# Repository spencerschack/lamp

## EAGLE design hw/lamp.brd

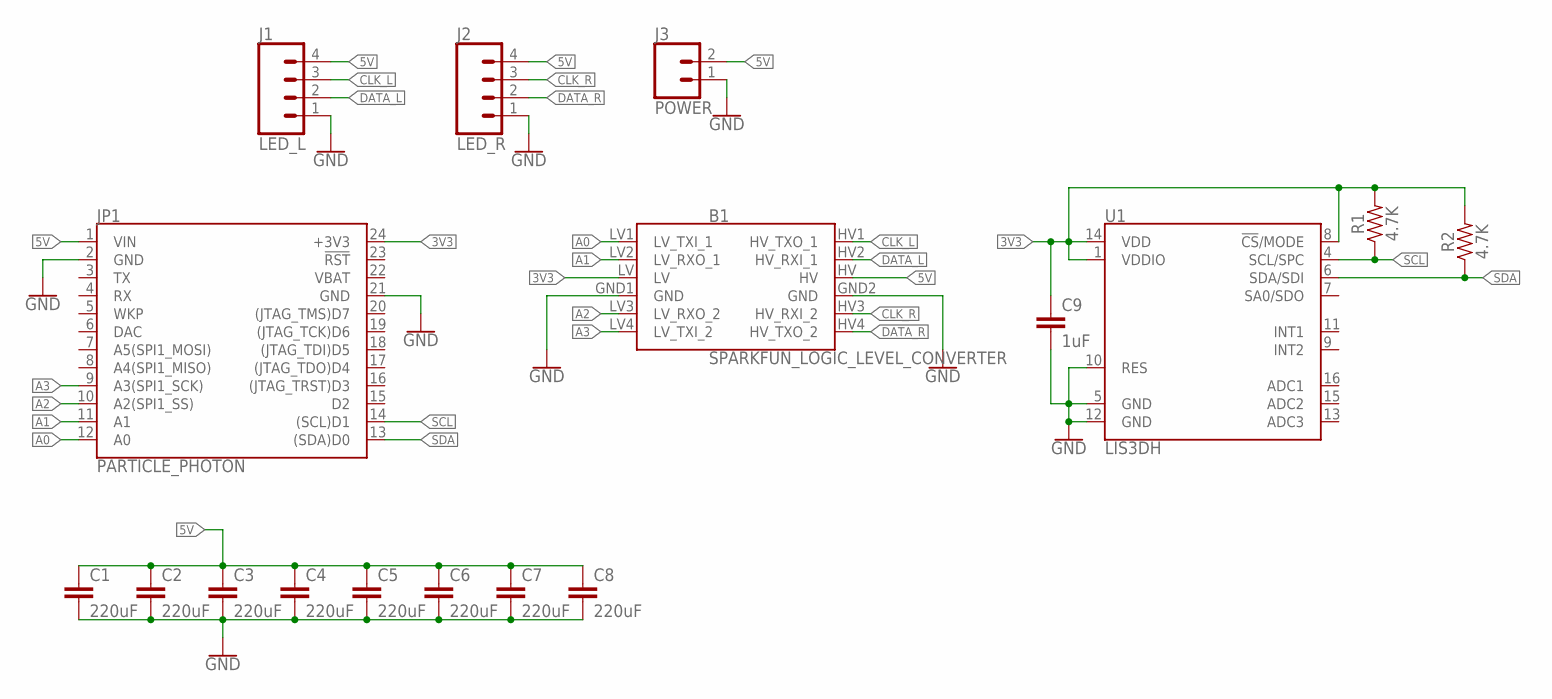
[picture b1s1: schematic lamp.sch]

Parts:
B1: SPARKFUN_LOGIC_LEVEL_CONVERTER
C1, C2, C3, C4, C5, C6, C7, C8: 220uF; 1206
C9: 1uF; 0603
J1: LED_L; 1X04_LONGPADS
J2: LED_R; 1X04_LONGPADS
J3: POWER; 1X02_LOCK_LONGPADS
JP1: PARTICLE_PHOTON
R1, R2: 4.7K; 0603
U1: LIS3DH; LGA-16-3X3

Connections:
3V3: B1.LV, C9.1, JP1.24 (+3V3), R1.2, R2.2, U1.1 (VDDIO), U1.8 (!CS!/MODE), U1.14 (VDD)
5V: B1.HV, C1.1, C2.1, C3.1, C4.1, C5.1, C6.1, C7.1, C8.1, J1.4, J2.4, J3.2, JP1.1 (VIN)
A0: B1.LV1 (LV_TXI_1), JP1.12 (A0)
A1: B1.LV2 (LV_RXO_1), JP1.11 (A1)
A2: B1.LV3 (LV_RXO_2), JP1.10 (A2(SPI1_SS))
A3: B1.LV4 (LV_TXI_2), JP1.9 (A3(SPI1_SCK))
CLK_L: B1.HV1 (HV_TXO_1), J1.3
CLK_R: B1.HV3 (HV_RXI_2), J2.3
DATA_L: B1.HV2 (HV_RXI_1), J1.2
DATA_R: B1.HV4 (HV_TXO_2), J2.2
GND: B1.GND1 (GND), B1.GND2 (GND), C1.2, C2.2, C3.2, C4.2, C5.2, C6.2, C7.2, C8.2, C9.2, J1.1, J2.1, J3.1, JP1.2 (GND), JP1.21 (GND), U1.5 (GND), U1.10 (RES), U1.12 (GND)
SCL: JP1.14 ((SCL)D1), R1.1, U1.4 (SCL/SPC)
SDA: JP1.13 ((SDA)D0), R2.1, U1.6 (SDA/SDI)
VBAT: JP1.22 (VBAT)

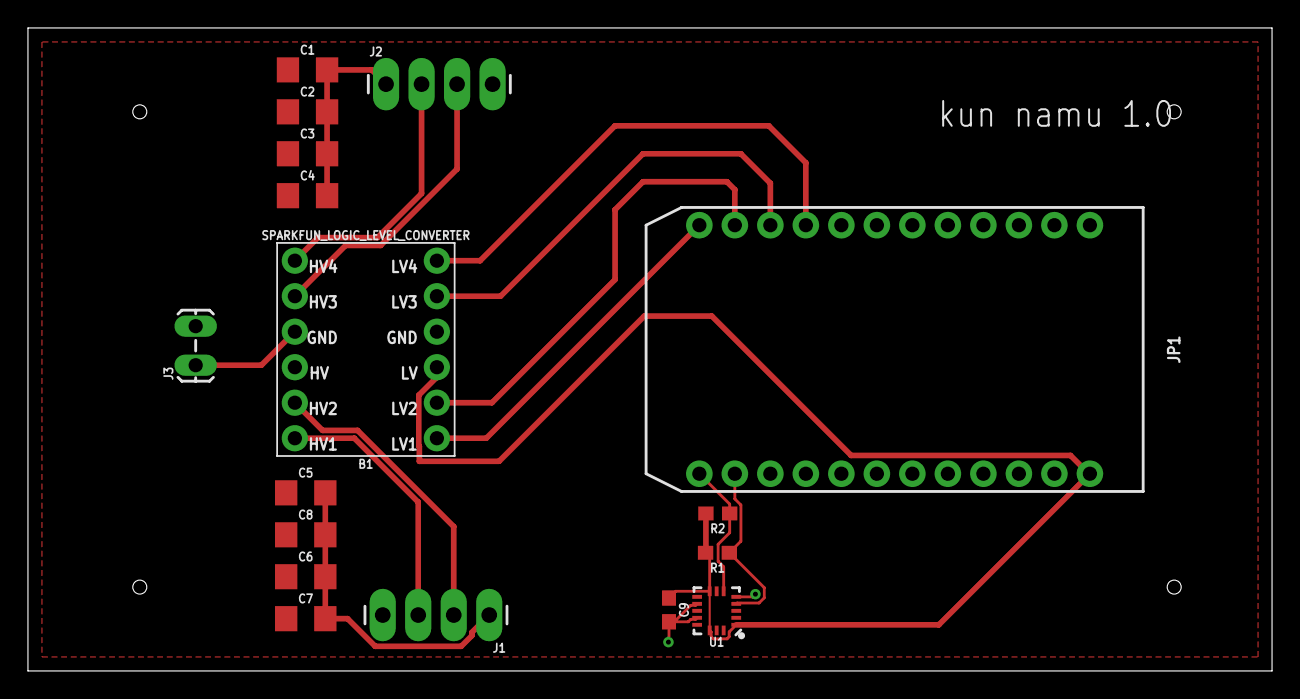
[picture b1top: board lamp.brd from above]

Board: 2 copper layers, 89.0 x 46.0 mm, 17 parts (0 on the bottom side), 13 nets.

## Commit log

2017-10-17 both sides
2017-10-18 lighting
2018-03-19 build
2018-03-19 Fixed the pin mappings, asshole.
2018-07-09 cool siney things
2018-07-20 Commit before I delete all the crap we don't use
2018-07-20 Things still compile
2018-10-20 All files
2019-05-19 Boot without WiFI and enable it later

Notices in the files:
parts and their libraries:
SparkFun-Boards: Licensing: Creative Commons ShareAlike 4.0 International - https://creativecommons.org/licenses/by-sa/4.0
